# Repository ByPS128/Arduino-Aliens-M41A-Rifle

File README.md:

# Welcome,

the project is a simple simulator of rifle and grenade launcher firing mockups of the popular M41A weapon from the legendary Aliens movie.
The hardware is implemented using an Arduino Nano and a DF Player (also known as the DF Robot) along with a few other peripherals.

#### In the document I will describe both HW and SW, browse it to the places you are interested in.

## So what does intended HW version consist of:

There are many M41A mock-ups on the market, including 3D printed ones. The version I was sounding did not have a working grenade launcher and it also did not have a retractable slide. We used the magazine space to house the electronics and so this version of the 3D printed rifle has quite a lot of limitations.
However, the software is easy to adapt for a larger application with multiple input signals.

* Arduino Nano
* DF Player for reproducing sounds
* Rotary Encoder with button to control volume, can be without button and it will work without the whole rotary encoder
* LED to illuminate the flashes in the barrel of the rifle
* LED to illuminate the barrel of the rifle
* Button to trigger the rifle's firing pin
* Button to trigger loading / firing of the grenade launcher
* Button to trigger the sound of the rifle bolt retracting
* Button to play magazine change sound
* Double digit 7 segment display
* Required resistors, capacitor and shocky protection diode

## 3D print
I made a 3D models of magazine foot where I placed:
* battery
* switch for turning on/off
* rotary encoder to adjust volume

You can use my 3D models for 3D printing if compatible with yours models of M41A rifle.

I will be glad if you use them, see here at Printables.com:

https://www.printables.com/cs/model/940214-m41a-rifle-magazine-foot-for-arduino-implementatio

I am using OnShape to create models, here is direct link if you are interested in:
https://cad.onshape.com/documents/143c32e288eb70a4674d24e8/v/e97b14a1ca8f76a05194cd48/e/891a4cec0397cb99cd8f56b7

## Want see how it works?
Here is updated video of the project in action with description of all functions:

https://www.youtube.com/watch?v=IwG0UBBIASA

## Schematic

I developed the scheme in KiCad (free). It's my first schematic, so please excuse me if I didn't choose some brands correctly. Alternatively, please modify the scheme and make a pull request. The schematic source files are in the KiCad directory.

https://www.kicad.org/

Schema preview:

## Schama descriptions about condensators used as filter of peaks and noise:
To prevent the display from flickering after switching on the circuit, or even a flicker in the speaker, I recommend using an electrolytic and ceramic capacitor in parallel. Each type has different characteristics and they complement each other:

* 100 µF electrolytic capacitor: This capacitor is able to smooth out low frequency peaks and provide a stable power supply. Electrolytic capacitors have high capacitance and are suitable for low frequency filtering.

* 100 nF ceramic capacitor: This capacitor is capable of smoothing out high frequency peaks and noise. Ceramic capacitors have lower capacitance but are faster and more efficient for filtering high frequencies.

### So you should use both types of capacitors in parallel:
* Electrolytic capacitor **C1** (100 µF) between VCC and GND.
* Ceramic capacitor **C2** (100 nF) between VCC and GND.

### The order of the capacitors in the direction from source to consumer matters:
1. Ceramic capacitor (100 nF): this capacitor should be as close as possible to the power pins of the components (i.e. to the consumers). Ceramic capacitors are able to quickly filter out high frequency noise, which is useful for removing fast changes and interference.
2. electrolytic capacitor (100 µF). Electrolytic capacitors have higher capacitance and are able to smooth out low frequency peaks and stabilize the power supply.

## Estimation of current consumption
### Components:
* Arduino Nano: approximately 50 mA
* DFPlayer Mini: approximately 150-250 mA (without speaker)
* Speaker: up to 600 mA (at maximum power)
* Display with 74HC595: approximately 50-100 mA
* Other components (LEDs, switches, etc.): approx. 20-50 mA

### Total estimated current consumption
Approximately 870-1050 mA (considering all components at maximum power)

Calculation of capacitor capacitance required
It is common practice for filter capacitors to use 100-200 µF for every 100 mA of current draw.

Electrolytic capacitor **C3**
Required capacitance: (1050 mA / 100 mA) * 100-200 µF = 1050-2100 µF
Ceramic capacitor **C4**
Capacitance required: 100 nF to 1 µF (for high frequency noise)

### Recommended capacitances for capacitor.

#### C3 (electrolytic capacitor)
Recommended capacitance: 1000 µF to 2200 µF
This value will provide sufficient power supply filtering for all components.

#### C4 (ceramic capacitor)
Recommended capacitance: 100 nF to 1 µF
This value will help with high frequency noise filtering.

Schema file resides here: /KiCad/M41A/M41A.kicad_sch

and here is PDF version: /KiCad/M41A-Schematic.pdf

If you would like to open the schema, import the libraries I created. I couldn't find schematic marks for some components, so I created them with their footprints.
The library is in the directory: /KiCad/Project_Library.kicad_sym

### DF Player

I decided to use DF Player for playing sounds for several reasons:

* Low purchase price
* The possibility of controlling the serial line with its own simple protocol
* Clear organization of sound files on the SD card
* A large number of existing compatible libraries to support the protocol

However hend I made the experience that not every clone works properly. I was unlucky and the very first one I bought was built on the `MH2024K-24SS` chip. This has huge latency from the instruction to play the audio to the actual start of playback takes a second.
And that's unusable. That's why I bought a few more from different stores and came across a module with a `TD5580A` chip and it responds instantly. And that's why I recommend you use it. 

I used the protocol handler from an existing library and modified it to suit me better.

### Speaker

I used a 3W speaker. The specification of the DF Player says that the built-in amplifier will drive the 3W speaker to the maximum.
If you wanted to use a more powerful speaker, you would have to insert another amplifier between the player and the speaker and use a separate power supply.

**You can find the documentation for the DF player in the DOC directory, including communication protocol specs.**

### 2 digit 7 segment display

For displaying the remaining bullets in the rifle's magazine, I used, how else, red segment displays. And to get rid of a bunch of wires and resistors, I used a driver that is beautifully compact, works perfectly.
It contains a 74HC595 circuit for each segment. The displays used shared anode, so the segment lights up when its pin is at logic zero.

https://www.aliexpress.us/item/3256805033000283.html

### Rotary Encoder with button

I used this one, with built-in RC filter. Thanks to the filter, the dream was not to treat false presses.

https://www.aliexpress.us/item/3256805548024336.html

### LED diods

I used high brightness 5mm, warm white, 30mA LEDs
https://www.gme.cz/v/1492064/OptoSupply-OSM5DK5201A-LED-5mm-tepla-bila

## What this module can do, how it was designed

* Pressing and holding the trigger of the rifle starts playing the sound of firing and with each round fired the LED flashes to simulate a flash. At the same time, each shot will be read from the counter.
* When all rounds have been fired, the display shows 00 and the sound of the hammer striking empty is heard.
* Each subsequent pull of the trigger with an empty magazine will play this sound.
* The slide release button will also cause the magazine to load to 95 and cause the slide release sound to play.
* The magazine change button will set the magazine count to 95 rounds and trigger the magazine change and slide release sound.
* the grenade launcher trigger button will load a grenade with one press and play a sound consisting of several: chamber opening, grenade insertion and chamber closing.
* another press of the grenade launcher trigger will fire the grenade and play the sound of the grenade being fired. At the same time, the time to wait for the grenade to explode is randomly calculated. The next press of the grenade launcher trigger repeats charge, shot, charge, shot, etc.
* Rotating the rotary encoder changes the volume. When the gun is at rest and you change the volume, the display shows the volume numbers. The volume can also be changed while the sounds are playing. If a firing sound is playing and you are changing the volume, the display shows the cartridge level in the magazine as a priority.
* Pressing/pushing on the rotary encoder has 2 functions. A short press shows the current volume value on the display. A long press (a second or more) causes the status to be entered 

## Other features:

I made some sounds in multiple variations. This is so that the simulation does not appear monotonous. So every time I start shooting, a different option comes up. They repeat over time, but for the shot I made it so that each new playback plays a different file.
Similarly, the pulling of the weapon's bolt is solved, the sound of squeezing the trigger with an empty magazine is also solved.

## Sounds on SD card

The program is somehow built and expects concrete files on the sd card. DF Player uses mtak that I select a directory and a file in it. This is defined by numbers. So the directories are numbered and always with two digits, i.e. "01". I don't use them anymore. It would be easy to use the rotary encoder to select a different directory and thus select a different set of sounds, and suddenly the sounds could be from a specific existing weapon, or totally crazy sci-fi sounds, etc. In directory 01 there are files that must also be numbered in 3 places, i.e. 001, 002, etc. In the constants of the application, it is then defined which number has which sound.
For example (excerpt from AppConstants.h)

```
// I have some sounds in multiple variants and I randomly choose which variant to play.
// For this there are FIRST and LAST containers, which define the file numbers of the sounds of a given type.

// Sound file interval for rifle fire
static const int SAMPLE_RIFLE_FIRE_FIRST = 1;
static const int SAMPLE_RIFLE_FIRE_LAST = 6;

// Sound file interval for cock sound
static const int SAMPLE_COCK_FIRST = 10;
static const int SAMPLE_COCK_LAST = 14;

// Sound file interval for empty magazine, you rpes rifle fire and this empty file will play
static const int SAMPLE_EMPTY_MAGAZINE_FIRST = 20;
static const int SAMPLE_EMPTY_MAGAZINE_LAST = 24;
```

## File list on SD card.

Files must start with a number, but can continue with any name that describes the sound.
This is what my SD card looks like:

```
001-Shoot-95.wav
002-Shoot-95.wav
003-Shoot-95.wav
004-Shoot-95.wav
005-Shoot-95.wav
006-Shoot-95.wav
010-Cock-01-Sniper.wav
011-Cock-02.wav
012-Cock-03.wav
013-Cock-04.wav
014-Cock-05.wav
020-Empty.wav
021-Empty.wav
022-Empty.wav
023-Empty.wav
024-Empty.wav
030-MagazineEject-01.wav
031-MagazineEject-02.wav
040-MagazineLoad-01.wav
041-MagazineLoad-02.wav
042-MagazineLoad-03.wav
050-MagazineReload-01.wav
051-MagazineReload-02.wav
053-MagazineReloadCock-01.wav
054-MagazineReloadCock-02.wav
060-GranadeFire-01.wav
061-GranadeFire-02.wav
062-GranadeFire-03.wav
065-GranadeLoad-01.wav
066-GranadeExplosion-01.wav
067-GranadeExplosion-02.wav
070-Volume-01-Down.wav
071-Volume-02-Down.wav
072-Volume-03-Down.wav
073-Volume-04-Down.wav
074-Volume-05-Down.wav
080-Volume-01-Up.wav
081-Volume-02-Up.wav
082-Volume-03-Up.wav
083-Volume-04-Up.wav
084-Volume-05-Up.wav
090-CardInserted.wav
091-CardRemoved.wav
092-LowBattery.wav
093-VolumeSaved.wav
094-WeaponReady.wav
095-Click-01.wav
```

But in reality, the application, as its source codes define, uses the following files:
(Starting to play unused sounds is commented out in the application.)

```
001-Shoot-95.wav
002-Shoot-95.wav
003-Shoot-95.wav
004-Shoot-95.wav
005-Shoot-95.wav
006-Shoot-95.wav
010-Cock-01-Sniper.wav
011-Cock-02.wav
012-Cock-03.wav
013-Cock-04.wav
014-Cock-05.wav
020-Empty.wav
021-Empty.wav
022-Empty.wav
023-Empty.wav
024-Empty.wav
053-MagazineReloadCock-01.wav
054-MagazineReloadCock-02.wav
060-GranadeFire-01.wav
065-GranadeLoad-01.wav
066-GranadeExplosion-01.wav
093-VolumeSaved.wav
```

It is also essential to use the DriveSort app: [Anerty's Lair - DriveSort](https://www.anerty.net/software/file/DriveSort/) which sorts the files on the SD card so that they are physically organized in sequence.
This has a major impact on the delay/latency before the sound starts playing.

## How I made the sounds.

I searched in sound banks which provides free sounds for free download and use.
For example, I searched for gun cocking sounds under the keyword "cock" and one of the many useful ones I found is, for example, this one:
https://artlist.io/sfx/track/battle-rifles---fn-fal-cocking-gun/80693

It will probably take you some time to find the right sounds that you will like and fit for your application.

The firing of the M41A rifle is specific sound and is difficult to imitate. So I bought the game "Aliens Colonial Marines" and used the sounds from it.

To edit the sounds, I used the AudaCity software, which is free and can do everything necessary in it.
[https://www.audacityteam.org/](https://www.audacityteam.org/)

## Audio file format

DF Player can play many formats including MP3 in CD quality and stereo.
(It even has a simple equalizer, but I haven't used it, but you can, I have implemented functions to adjust the equalizer, just use them.)

The connection I used is monophonic, so using files containing stereo tracks is unnecessary workload for DF Player, and also such files are larger, which means that more power and time are needed to upload and process the file.
And this app (M41A) works well only when it responds instantly.
So, for these reasons, even after several attempts and tests, I decidedto use uncompresed WAV format, 8bit, mono with 22050 sample rate.
It sounds as good from that 3W speaker as the 16bit mono 44100. If you used a better speaker, then it is possible that you would use a better quality sound.

If you would use better quality sounds, there is no need to change anything in the application. The detection of the audio file format is fully under the control of DF Player.

When I wrote about organizing files on the SD card above, I mentioned the 01 directory that I use.
But you can easily have more such directories and the same numbered files in them. These can contain the same but higher quality sounds. By simply changing the value of one constant, you tell the application to use a different directory. And so you can easily test which sounds are better in your application.
The constant is named `DEFAULT_DIRECTORY_NUMBER` and resides in DFPlay.h file

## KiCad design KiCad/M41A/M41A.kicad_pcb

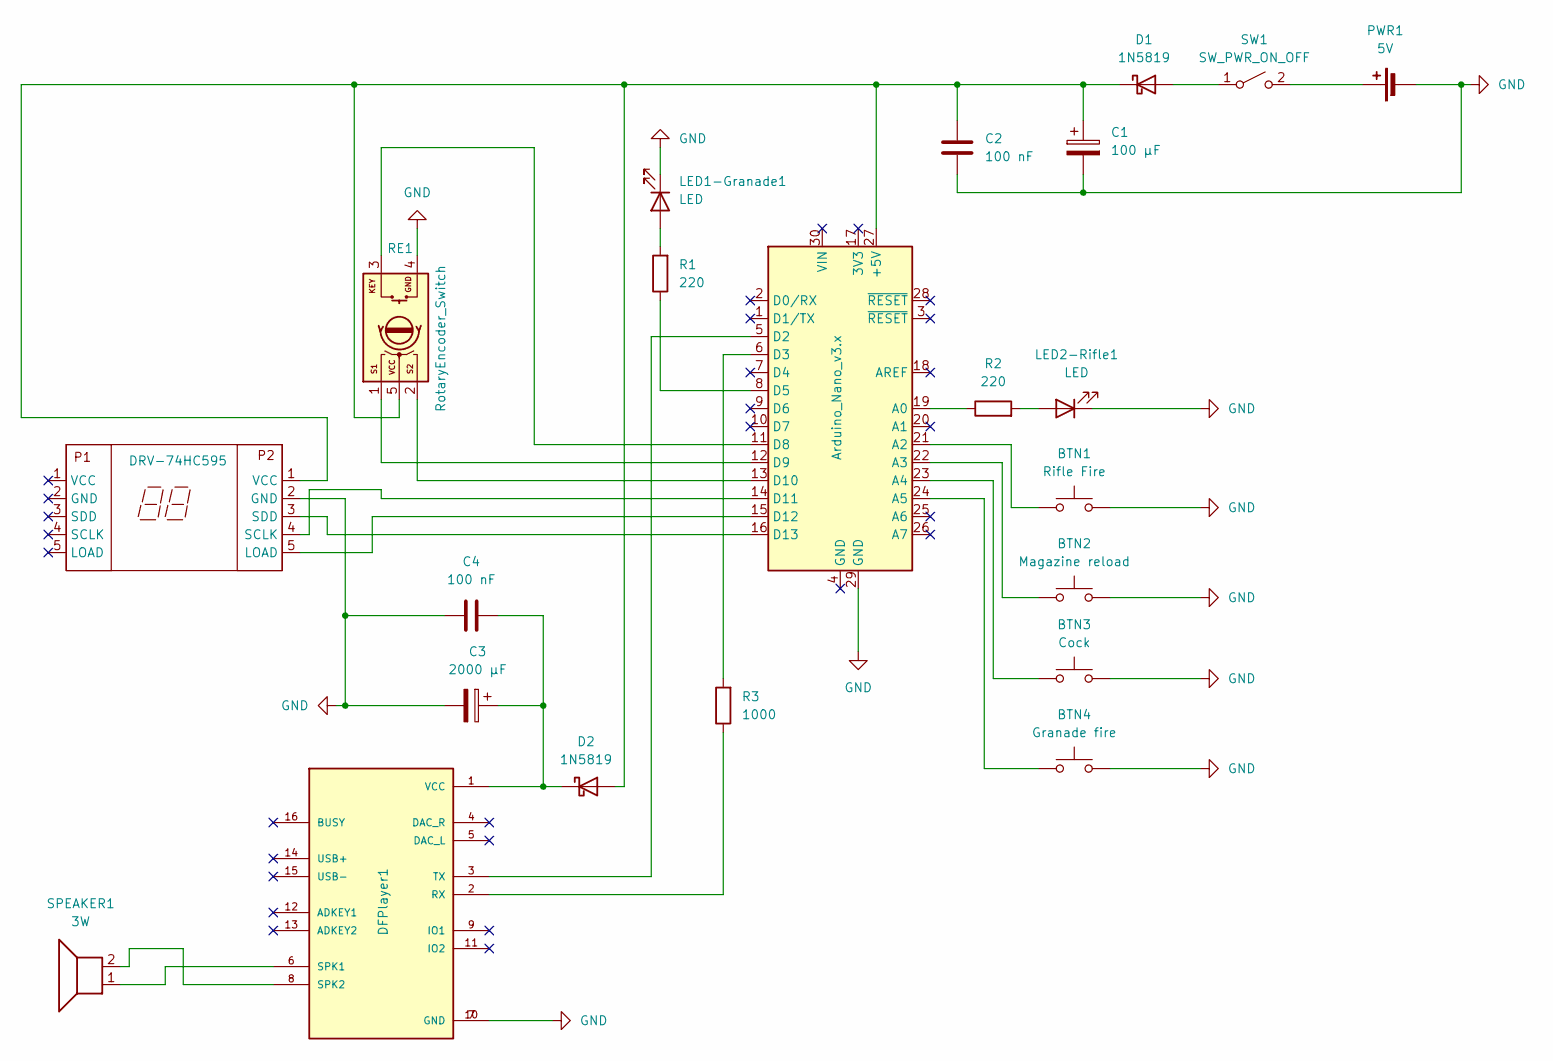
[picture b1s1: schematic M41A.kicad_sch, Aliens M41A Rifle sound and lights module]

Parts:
A1: Arduino_Nano_v3.x; Arduino_Nano
BTN1: Rifle Fire; Button Leads 2x 2.54
BTN2: Magazine reload; Button Leads 2x 2.54
BTN3: Cock; Button Leads 2x 2.54
BTN4: Granade fire; Button Leads 2x 2.54
C1: 100 µF; CP_Radial_D5.0mm_P2.50mm
C2, C4: 100 nF; C_Rect_L4.0mm_W2.5mm_P2.50mm
C3: 2000 µF; CP_Radial_D5.0mm_P2.50mm
D1, D2: 1N5819; D_DO-41_SOD81_P10.16mm_Horizontal
DFPlayer1: DFPlayer; MODULE_DFR0299
DRV-74HC595: Segment Display Leads 5x 2.54
LED1-Granade1, LED2-Rifle1: LED; LED Leads 2x 2.54
PWR1: 5V; Battery 4x 2.54
R1, R2: 220; R_Axial_DIN0204_L3.6mm_D1.6mm_P7.62mm_Horizontal
R3: 1000; R_Axial_DIN0204_L3.6mm_D1.6mm_P7.62mm_Horizontal
RE1: RotaryEncoder_Switch; RotaryEncoder Leads 5x 2.54
SPEAKER1: 3W; Speaker Leads 2x 2.54
SW1: SW_PWR_ON_OFF; SW_DIP_SPSTx01_Piano_10.8x4.1mm_W7.62mm_P2.54mm

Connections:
GND: A1.29 (GND), BTN1.2, BTN2.2, BTN3.2, BTN4.2, C1.2, C2.2, C3.2, C4.1, DFPlayer1.7 (GND), DFPlayer1.10 (GND), DRV-74HC595.2 (GND), LED1-Granade1.1 (K), LED2-Rifle1.1 (K), PWR1.2 (-), RE1.4 (GND)
unnamed: A1.27 (+5V), C1.1, C2.1, D1.1 (K), D2.2 (A), DRV-74HC595.1 (VCC), RE1.5 (VCC)
unnamed: A1.19 (A0), R2.1
unnamed: A1.21 (A2), BTN1.1
unnamed: A1.22 (A3), BTN2.1
unnamed: A1.23 (A4), BTN3.1
unnamed: A1.24 (A5), BTN4.1
unnamed: A1.5 (D2), DFPlayer1.3 (TX)
unnamed: A1.6 (D3), R3.2
unnamed: A1.8 (D5), R1.1
unnamed: A1.11 (D8), RE1.3 (KEY)
unnamed: A1.12 (D9), RE1.1 (S1)
unnamed: A1.13 (D10), RE1.2 (S2)
unnamed: A1.14 (D11), DRV-74HC595.4 (SCLK)
unnamed: A1.15 (D12), DRV-74HC595.5 (LOAD)
unnamed: A1.16 (D13), DRV-74HC595.3 (SDD)
unnamed: D1.2 (A), SW1.1 (A)
unnamed: C3.1, C4.2, D2.1 (K), DFPlayer1.1 (VCC)
unnamed: DFPlayer1.2 (RX), R3.1
unnamed: DFPlayer1.6 (SPK1), SPEAKER1.1
unnamed: DFPlayer1.8 (SPK2), SPEAKER1.2
unnamed: LED1-Granade1.2 (A), R1.2
unnamed: LED2-Rifle1.2 (A), R2.2
unnamed: PWR1.1 (+), SW1.2 (B)

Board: 2 copper layers, 22 parts (0 on the bottom side), 24 nets, no tracks yet.

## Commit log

2024-05-09 Volume button behavior change. it rcognize short and long press now.
2024-05-09 Separation of M41A rifle sound player methods from DF player and its low level communication with HW.
2024-05-18 added new functionality of granade, better time management
2024-05-20 Added CiCad schematic and PCB
2024-05-20 Actrualized KiCad project library.
2024-05-20 Little chage in connection to key pin of rotary encoder.
2024-05-22 +KiCad schematic files
2024-05-22 Create LICENSE
2024-05-22 unwanted forgotten files removed
2024-05-22 Little naming refactor + some translated comments
2024-05-22 Readme, v1.1
2024-05-22 readme v1.2
2024-05-24 Division of the code into logical classes for better clarity and readability of the main simulator code.
2024-05-24 Comments transalation.
2024-05-24 added display animator, first initial version
2024-05-24 Weapon init animations at numbers display. looks sweet ;)
2024-05-24 Fine-tuning initialization to perfection.
2024-05-24 better display init with out segments blinks
2024-05-28 Actualized schema
2024-06-01 Optimization and refactor of classes, constants, encapsulation of constants to objects to which they belong, etc.
2024-06-01 Updated scheme
2024-06-14 Long press button fix. Minor improvements to the StopPlayback command..
2024-06-16 Addes images of good chips of DF player and alno of bad chips. Added product spec of Adjustable Step-down Buck Converter 2A
2024-06-16 Renaming some files and translating some contents to english language.
2024-06-17 Corrected schema wiring between arduino and df player.
2024-06-17 Update README.md - schematic correction
2024-06-17 Colored schematic wiring for better orientation.
2024-06-19 Better app start, speaker first weapon cock after turning on sometimes played at full volume because it didn't accept the volume setting.
2024-06-19 Releasing the rifle trigger will not stop the Empty sound from playing if the magazine is out of ammo.
